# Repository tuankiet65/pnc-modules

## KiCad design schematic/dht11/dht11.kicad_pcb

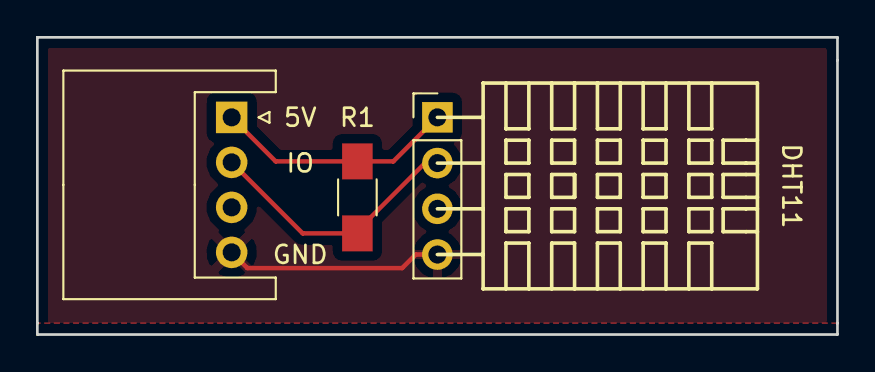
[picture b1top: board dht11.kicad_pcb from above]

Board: 2 copper layers, 44.5 x 16.5 mm, 3 parts (0 on the bottom side), 3 nets.

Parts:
J1: Conn_01x04; JST_XH_S04B-XH-A_04x2.50mm_Angled
R1: 10k; R_1206_HandSoldering
U1: DHT11; Pin_Header_Straight_1x04_Pitch2.54mm

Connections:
+5V: J1.1, R1.2, U1.1
/IO: J1.2, R1.1, U1.2
GND: J1.4, U1.4

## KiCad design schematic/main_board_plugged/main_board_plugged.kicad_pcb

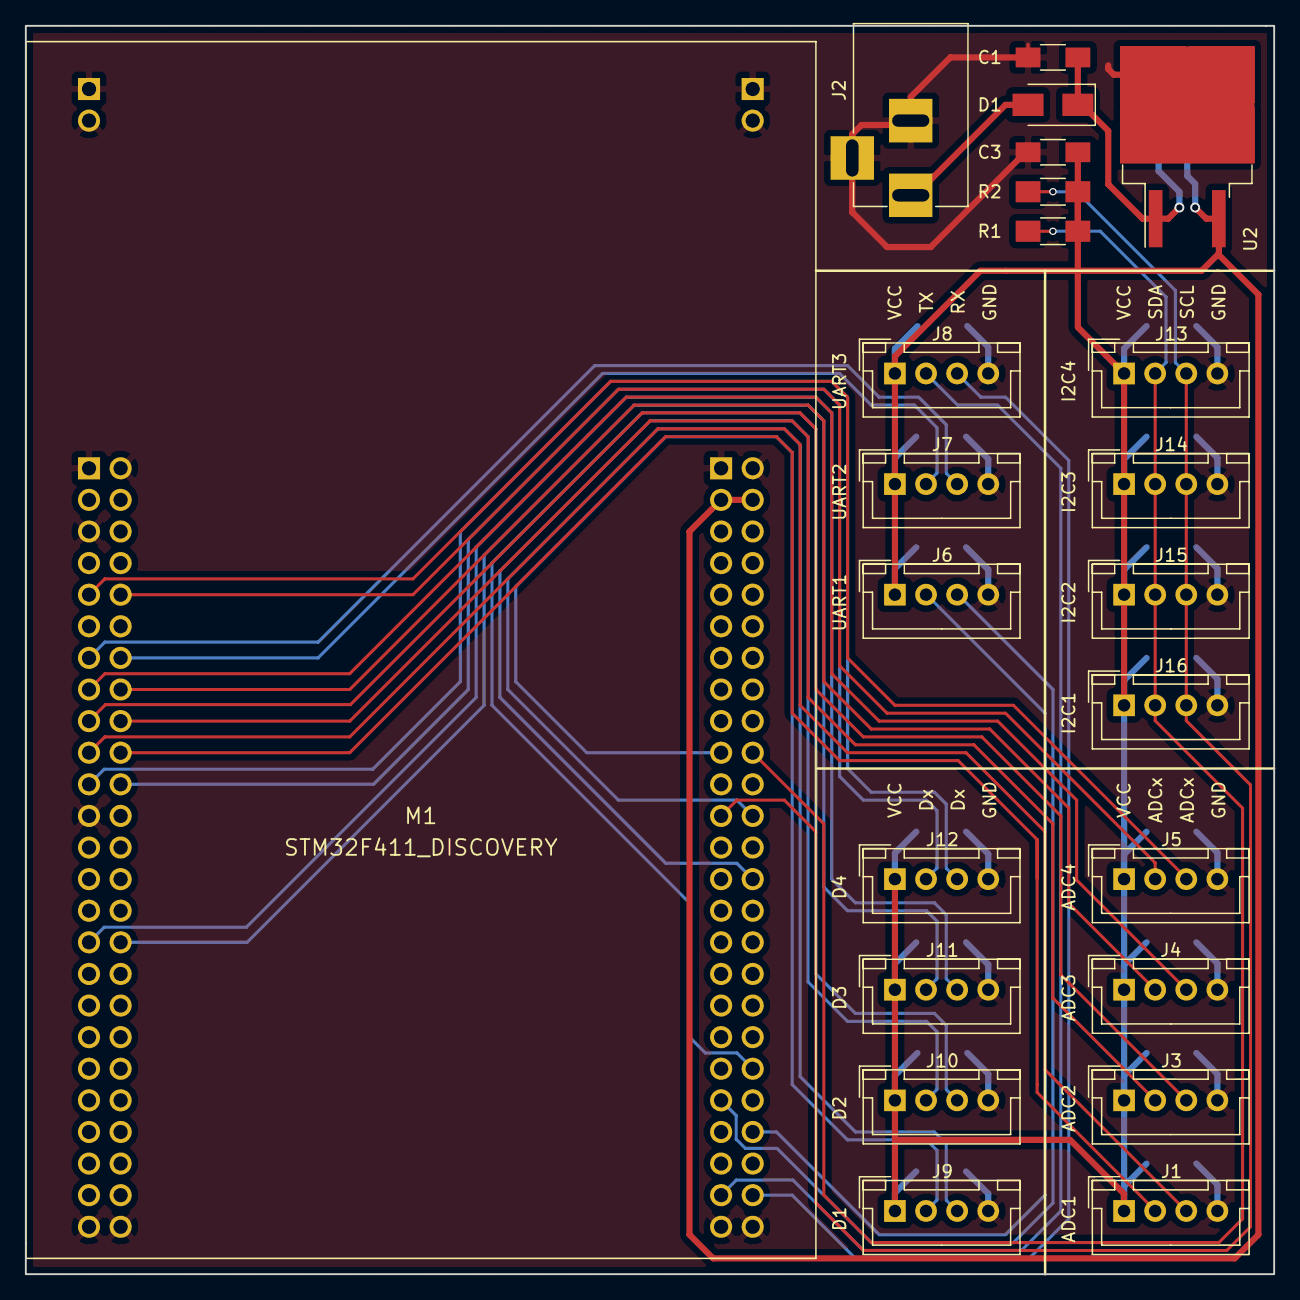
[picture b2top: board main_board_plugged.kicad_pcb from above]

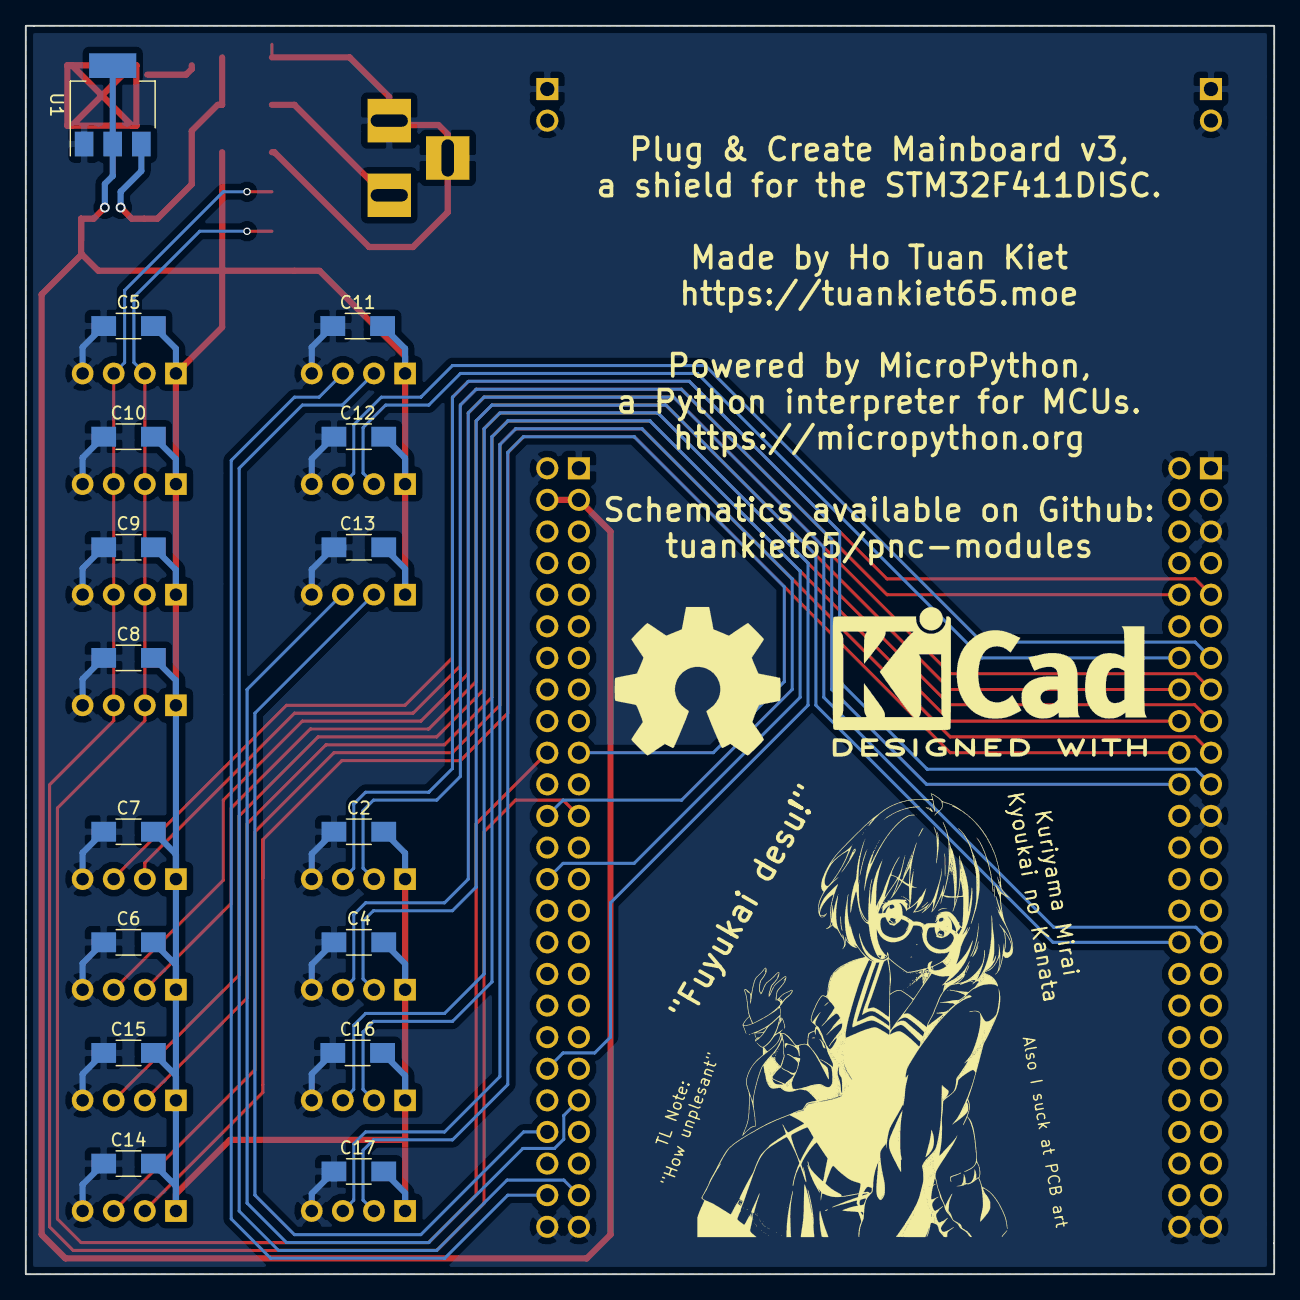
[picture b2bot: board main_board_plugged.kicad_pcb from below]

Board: 2 copper layers, 100.3 x 100.3 mm, 39 parts (16 on the bottom side), 28 nets.

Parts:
C1, C2, C4, C5, C6, C7, C8, C9, C10, C11, C12, C13, C14, C15, C16, C17: 100n; C_1206_HandSoldering
C3: 10u; C_1206_HandSoldering
D1: SS34; D_SMA
J1, J3, J4, J5, J6, J7, J8, J9, J10, J11, J12, J13, J14, J15, J16: Conn_01x04; JST_XH_B04B-XH-A_04x2.50mm_Straight
J2: Barrel_Jack; BARREL_JACK
M1: STM32F411_DISCOVERY; STM32F411_DISCOVERY-STM32F411_DISCOVERY
R1, R2: 10k; R_1206_HandSoldering
U1: LD1117S50TR_SOT223; SOT-223-3_TabPin2
U2: L7805; TO-263-2

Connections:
+5V: C2.1, C3.1, C4.1, C5.1, C6.1, C7.1, C8.1, C9.1, C10.1, C11.1, C12.1, C13.1, C14.1, C15.1, C16.1, C17.1, J1.1, J3.1, J4.1, J5.1, J6.1, J7.1, J8.1, J9.1, J10.1, J11.1, J12.1, J13.1, J14.1, J15.1, J16.1, M1.52, M1.77, R1.2, R2.2, U1.2, U2.3
/ADC1: J1.2, M1.35
/ADC2: J1.3, M1.10
/ADC3: J3.2, M1.34
/ADC4: J3.3, M1.9
/ADC5: J4.2, M1.33
/ADC6: J4.3, M1.8
/ADC7: J5.2, M1.30
/ADC8: J5.3, M1.5
/D1: J9.2, M1.60
/D2: J9.3, M1.87
/D3: J10.2, M1.89
/D4: J10.3, M1.95
/D5: J11.2, M1.41
/D6: J11.3, M1.16
/D7: J12.2, M1.36
/D8: J12.3, M1.11
/I2C1_SCL: J13.3, J14.3, J15.3, J16.3, M1.62, R2.1
/I2C1_SDA: J13.2, J14.2, J15.2, J16.2, M1.85, R1.1
/RX1: J6.3, M1.71
/RX2: J7.3, M1.7
/RX3: J8.3, M1.99
/TX1: J6.2, M1.97
/TX2: J7.2, M1.32
/TX3: J8.2, M1.74
GND: C1.2, C2.2, C3.2, C4.2, C5.2, C6.2, C7.2, C8.2, C9.2, C10.2, C11.2, C12.2, C13.2, C14.2, C15.2, C16.2, C17.2, J1.4, J2.2, J2.3, J3.4, J4.4, J5.4, J6.4, J7.4, J8.4, J9.4, J10.4, J11.4, J12.4, J13.4, J14.4, J15.4, J16.4, M1.1, M1.3, M1.12, M1.25, M1.26, M1.50, M1.51, M1.75, M1.76, M1.100, M1.101, M1.102, M1.103, M1.104, U1.1, U2.2
unnamed: C1.1, D1.1, U1.3, U2.1
VCC: D1.2, J2.1

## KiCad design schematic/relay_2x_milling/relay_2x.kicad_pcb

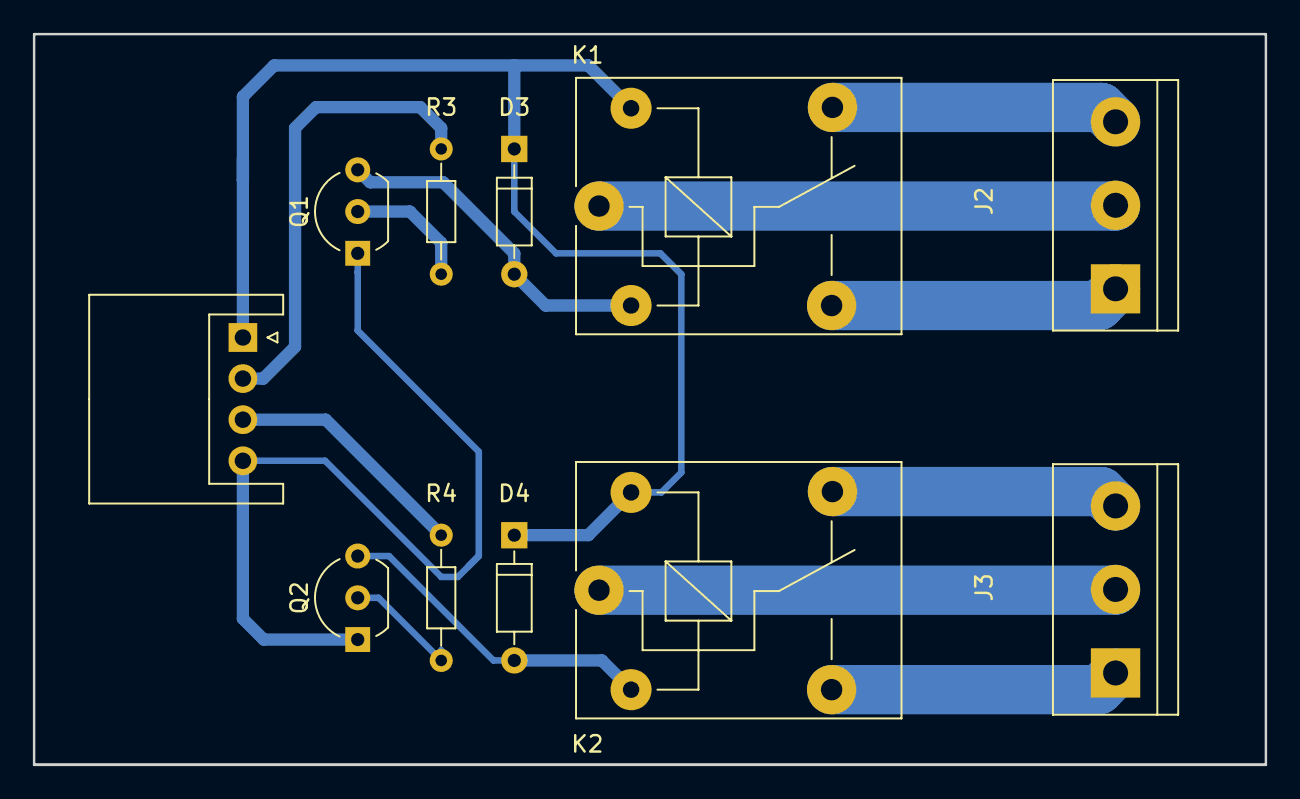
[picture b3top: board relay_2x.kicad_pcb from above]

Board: 2 copper layers, 74.9 x 44.5 mm, 11 parts (0 on the bottom side), 14 nets.

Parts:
D3, D4: 1N4007; D_DO-35_SOD27_P7.62mm_Horizontal
J1: Conn_01x04; JST_XH_S04B-XH-A_04x2.50mm_Angled
J2, J3: Conn_01x03; TerminalBlock_bornier-3_P5.08mm
K1, K2: SANYOU_SRD_Form_C; Relay_SPDT_SANYOU_SRD_Series_Form_C
Q1, Q2: 2N3904; TO-92_Inline_Wide
R3, R4: 1k; R_Axial_DIN0204_L3.6mm_D1.6mm_P7.62mm_Horizontal

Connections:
+5V: D3.1, D4.1, J1.1, K1.5, K2.5
/RELAY1: J1.2, R3.2
/RELAY2: J1.3, R4.2
GND: J1.4, Q1.1, Q2.1
unnamed: D3.2, K1.2, Q1.3
unnamed: D4.2, K2.2, Q2.3
unnamed: J2.1, K1.3
unnamed: J2.2, K1.1
unnamed: J2.3, K1.4
unnamed: J3.1, K2.3
unnamed: J3.2, K2.1
unnamed: J3.3, K2.4
unnamed: Q1.2, R3.1
unnamed: Q2.2, R4.1

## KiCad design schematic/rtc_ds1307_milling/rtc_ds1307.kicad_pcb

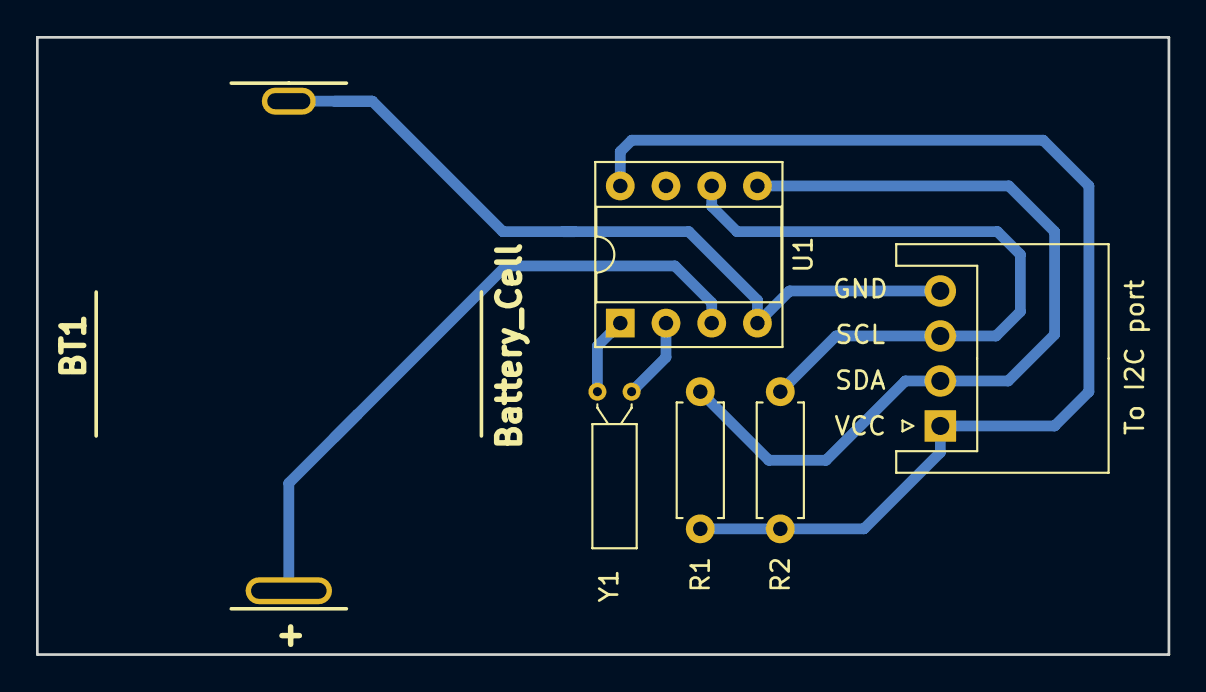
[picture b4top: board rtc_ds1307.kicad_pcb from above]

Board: 2 copper layers, 62.9 x 34.3 mm, 6 parts (0 on the bottom side), 7 nets.

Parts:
BT1: Battery_Cell; BC2032-E2
J1: Conn_01x04; JST_XH_S04B-XH-A_04x2.50mm_Angled
R1, R2: 10k; R_Axial_DIN0207_L6.3mm_D2.5mm_P7.62mm_Horizontal
U1: DS1307+; DIP-8_W7.62mm_Socket
Y1: 32768; Crystal_C26-LF_d2.1mm_l6.5mm_Horizontal

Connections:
+5V: J1.1, R1.1, R2.1, U1.8
+BATT: BT1.1, U1.3
-BATT: BT1.2, J1.4, U1.4
/SCL: J1.3, R2.2, U1.6
/SDA: J1.2, R1.2, U1.5
/XTAL1: U1.1, Y1.1
/XTAL2: U1.2, Y1.2

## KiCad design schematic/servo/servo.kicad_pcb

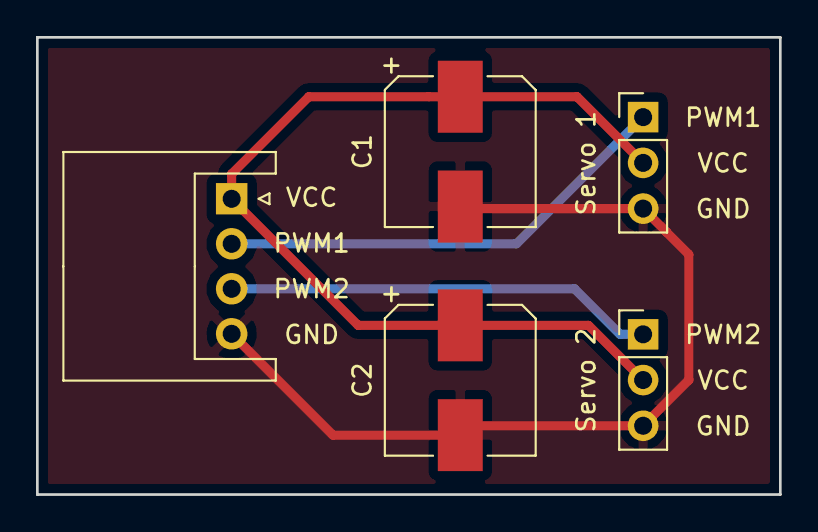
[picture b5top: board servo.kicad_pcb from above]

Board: 2 copper layers, 41.3 x 25.4 mm, 5 parts (0 on the bottom side), 4 nets.

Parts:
C1, C2: 470u; CP_Elec_8x10.5
J1: Conn_01x04; JST_XH_S04B-XH-A_04x2.50mm_Angled
M1: Servo1; Pin_Header_Straight_1x03_Pitch2.54mm
M2: Servo2; Pin_Header_Straight_1x03_Pitch2.54mm

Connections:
+5V: C1.1, C2.1, J1.1, M1.2, M2.2
/PWM1: J1.2, M1.1
/PWM2: J1.3, M2.1
GND: C1.2, C2.2, J1.4, M1.3, M2.3

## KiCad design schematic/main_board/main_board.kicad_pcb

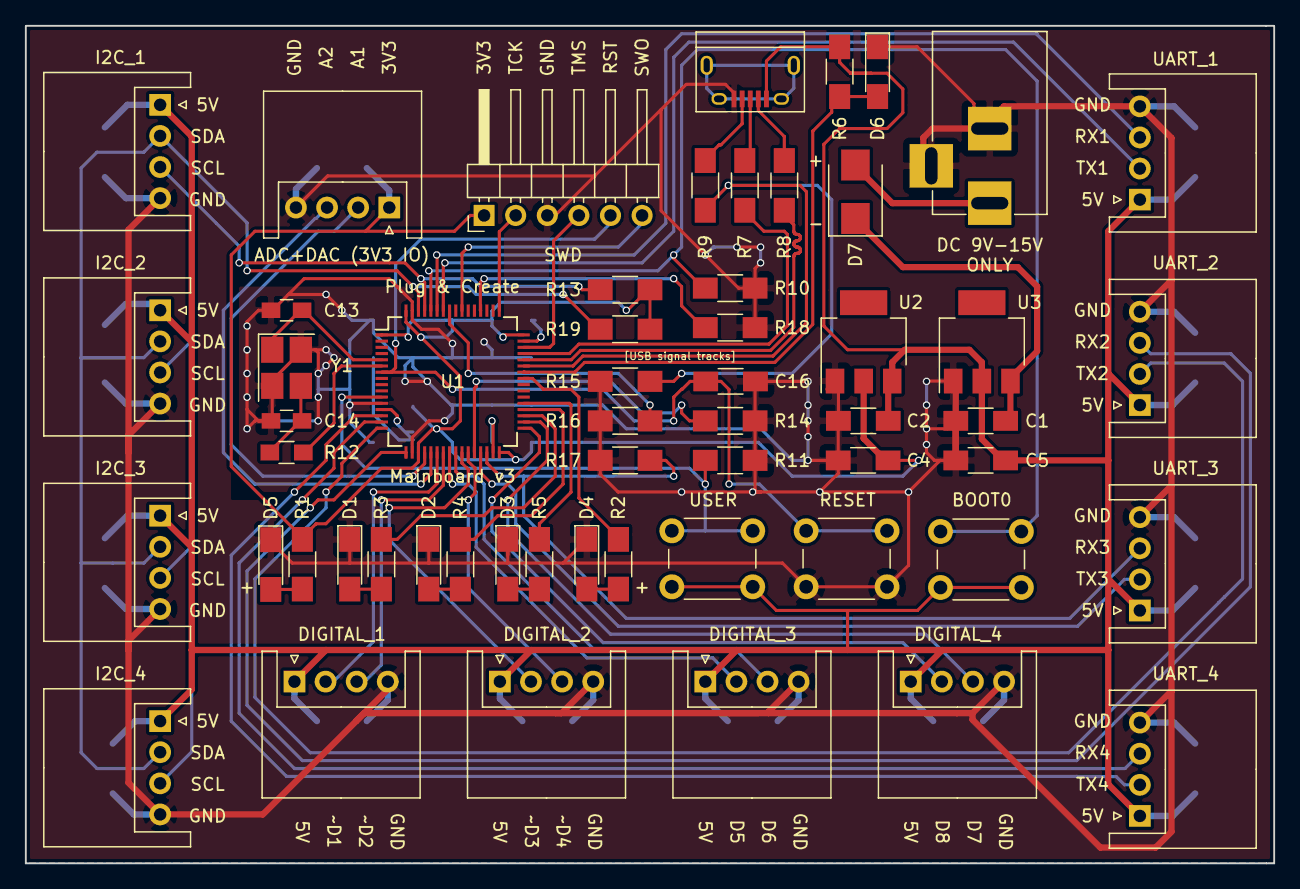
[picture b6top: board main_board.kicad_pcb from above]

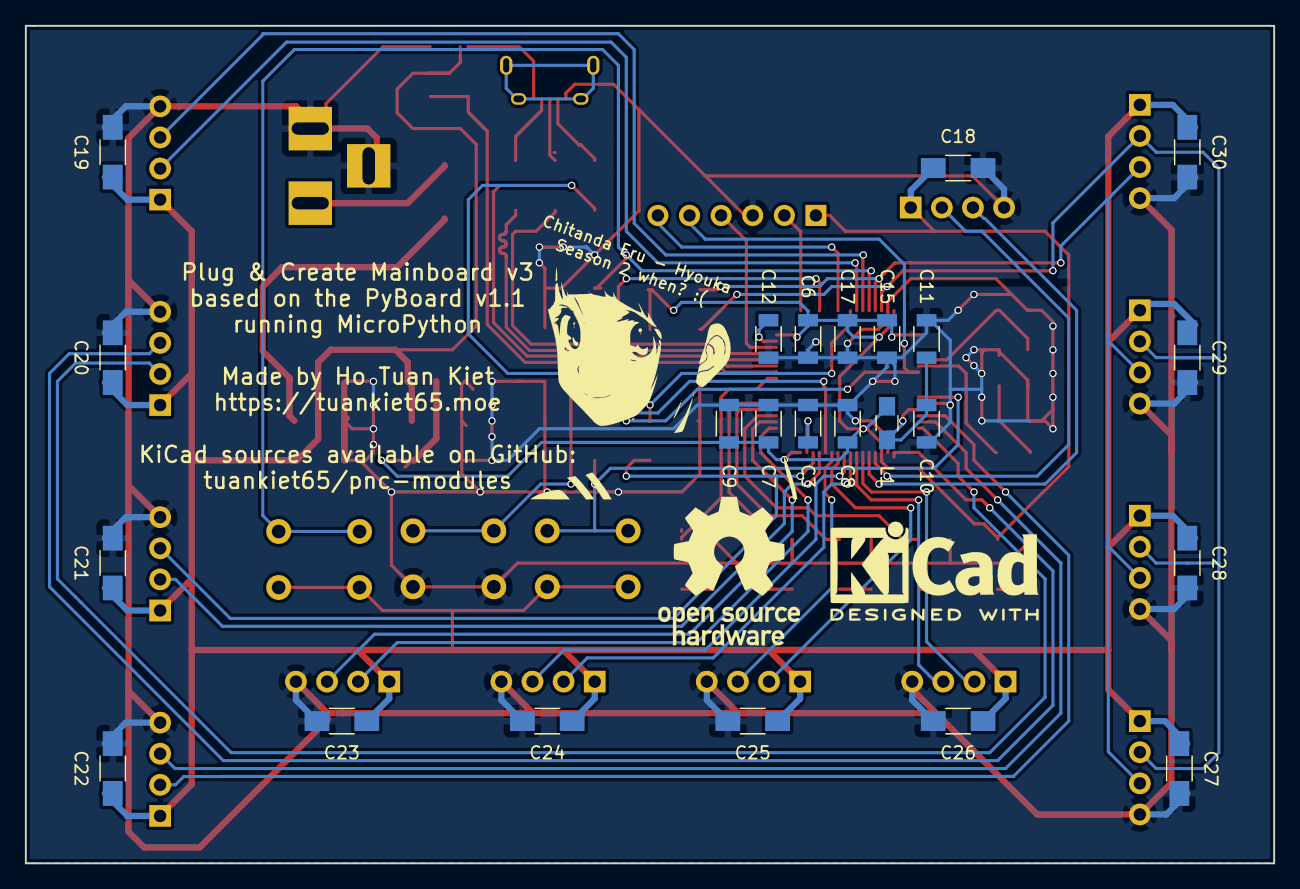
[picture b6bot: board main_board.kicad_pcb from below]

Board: 2 copper layers, 100.3 x 67.3 mm, 80 parts (24 on the bottom side), 56 nets.

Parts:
C1, C2, C16, C18, C19, C20, C21, C22, C23, C24, C25, C26, C27, C28, C29, C30: 100n; C_1206_HandSoldering
C3, C12: 2.2u; C_1206
C4, C5: 10u; C_1206_HandSoldering
C6, C7, C8, C10, C15, C17: 100n; C_1206
C9: 10u; C_1206
C11: 1u; C_1206
C13, C14: 5.6p; C_0805_HandSoldering
D1: RED; LED_1206_HandSoldering
D2, D5, D6: GREEN; LED_1206_HandSoldering
D3: BLUE; LED_1206_HandSoldering
D4: WHITE; LED_1206_HandSoldering
D7: SS34; D_SMB
J1: UART_1; JST_XH_S04B-XH-A_04x2.50mm_Angled
J2: UART_2; JST_XH_S04B-XH-A_04x2.50mm_Angled
J3: UART_3; JST_XH_S04B-XH-A_04x2.50mm_Angled
J4: UART_4; JST_XH_S04B-XH-A_04x2.50mm_Angled
J5: DIGITAL_1; JST_XH_S04B-XH-A_04x2.50mm_Angled
J6: DIGITAL_2; JST_XH_S04B-XH-A_04x2.50mm_Angled
J7: DIGITAL_3; JST_XH_S04B-XH-A_04x2.50mm_Angled
J8: DIGITAL_4; JST_XH_S04B-XH-A_04x2.50mm_Angled
J9: I2C_1; JST_XH_S04B-XH-A_04x2.50mm_Angled
J10: I2C_2; JST_XH_S04B-XH-A_04x2.50mm_Angled
J11: I2C_3; JST_XH_S04B-XH-A_04x2.50mm_Angled
J12: I2C_4; JST_XH_S04B-XH-A_04x2.50mm_Angled
J13: USB_OTG; USB_Micro-B
J14: ANALOG; JST_XH_S04B-XH-A_04x2.50mm_Angled
J15: SWD; Pin_Header_Angled_1x06_Pitch2.54mm
J17: Barrel_Jack; BARREL_JACK
L1: 600; L_0805_HandSoldering
R1, R2, R3, R4, R5: 220; R_1206_HandSoldering
R6, R9: 560; R_1206_HandSoldering
R7, R8: 22; R_1206_HandSoldering
R10, R11, R13, R14, R15, R16, R17, R18, R19: 10k; R_1206_HandSoldering
R12: 2k2; R_0805_HandSoldering
SW1: BOOT0; SW_PUSH_6mm
SW2: USR; SW_PUSH_6mm
SW3: RST; SW_PUSH_6mm
U1: STM32F405RGTx; LQFP-64_10x10mm_Pitch0.5mm
U2: LD1117S33CTR; SOT-223
U3: LD1117S50CTR; SOT-223
Y1: 12MHz; Crystal_SMD_3225-4pin_3.2x2.5mm_HandSoldering

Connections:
+3V3: C4.1, C6.1, C7.1, C8.1, C9.1, C15.1, C17.1, C18.1, J14.1, J15.1, L1.1, R1.2, R13.1, R19.1, U1.1, U1.19, U1.32, U1.48, U1.64, U2.2
+5V: C2.1, C5.1, C19.1, C20.1, C21.1, C22.1, C23.1, C24.1, C25.1, C26.1, C27.1, C28.1, C29.1, C30.1, J1.1, J2.1, J3.1, J4.1, J5.1, J6.1, J7.1, J8.1, J9.1, J10.1, J11.1, J12.1, J13.1, R6.2, SW1.2, SW2.2, U2.3, U3.2
/ANALOG1: J14.2, U1.20
/ANALOG2: J14.3, U1.21
/BOOT0: R10.1, SW1.1, U1.60
/D1: J5.2, U1.22
/D2: J5.3, U1.23
/D3: J6.2, U1.26
/D4: J6.3, U1.27
/D5: J7.2, U1.24
/D6: J7.3, U1.25
/D7: J8.2, U1.33
/D8: J8.3, U1.34
/HSE_IN: C13.1, U1.5, Y1.1
/HSE_OUT: R12.1, U1.6
/I2C1_SCL: J9.3, J10.3, J11.3, J12.3, R13.2, U1.61
/I2C1_SDA: J9.2, J10.2, J11.2, J12.2, R19.2, U1.62
/JTCK_SWCLK: J15.2, U1.49
/JTDO_SWO: J15.6, U1.55
/JTMS_SWDIO: J15.4, U1.46
/LED_BLUE: R5.2, U1.37
/LED_GREEN: R4.2, U1.36
/LED_RED: R3.2, U1.35
/LED_WHITE: R2.2, U1.41
/MICROSD_D3: R18.2, U1.52
/NRST: C16.1, J15.5, SW3.1, U1.7
/PB5: R16.2, U1.57
/RX1: J1.3, U1.59
/RX2: J2.3, U1.17
/RX3: J3.3, R17.2, U1.30
/RX4: J4.3, U1.15
/TX1: J1.2, U1.58
/TX2: J2.2, U1.16
/TX3: J3.2, U1.29
/TX4: J4.2, U1.14
/USB_D+: R7.1, U1.45
/USB_D-: R8.1, U1.44
/USB_ID: R9.1, R15.2, U1.43
/USB_VBUS: D6.2, R6.1, U1.42
/USER_BUTTON: R11.1, SW2.1, U1.11
/VCAP1: C3.1, U1.31
/VCAP2: C12.1, U1.47
GND: C1.2, C2.2, C3.2, C4.2, C5.2, C6.2, C7.2, C8.2, C9.2, C10.2, C11.2, C12.2, C13.2, C14.2, C15.2, C16.2, C17.2, C18.2, C19.2, C20.2, C21.2, C22.2, C23.2, C24.2, C25.2, C26.2, C27.2, C28.2, C29.2, C30.2, D1.1, D2.1, D3.1, D4.1, D5.1, D6.1, J1.4, J2.4, J3.4, J4.4, J5.4, J6.4, J7.4, J8.4, J9.4, J10.4, J11.4, J12.4, J13.5, J14.4, J15.3, J17.2, J17.3, R10.2, R11.2, R14.1, R15.1, R16.1, R17.1, R18.1, SW3.2, U1.12, U1.18, U1.63, U2.1, U3.1, Y1.2, Y1.4
unnamed: C1.1, D7.1, U3.3
unnamed: C14.1, R12.2, Y1.3
unnamed: D1.2, R3.1
unnamed: D2.2, R4.1
unnamed: D3.2, R5.1
unnamed: D4.2, R2.1
unnamed: D5.2, R1.1
unnamed: D7.2, J17.1
unnamed: J13.2, R8.2
unnamed: J13.3, R7.2
unnamed: J13.4, R9.2
unnamed: R14.2, U1.28
VDDA: C10.1, C11.1, L1.2, U1.13

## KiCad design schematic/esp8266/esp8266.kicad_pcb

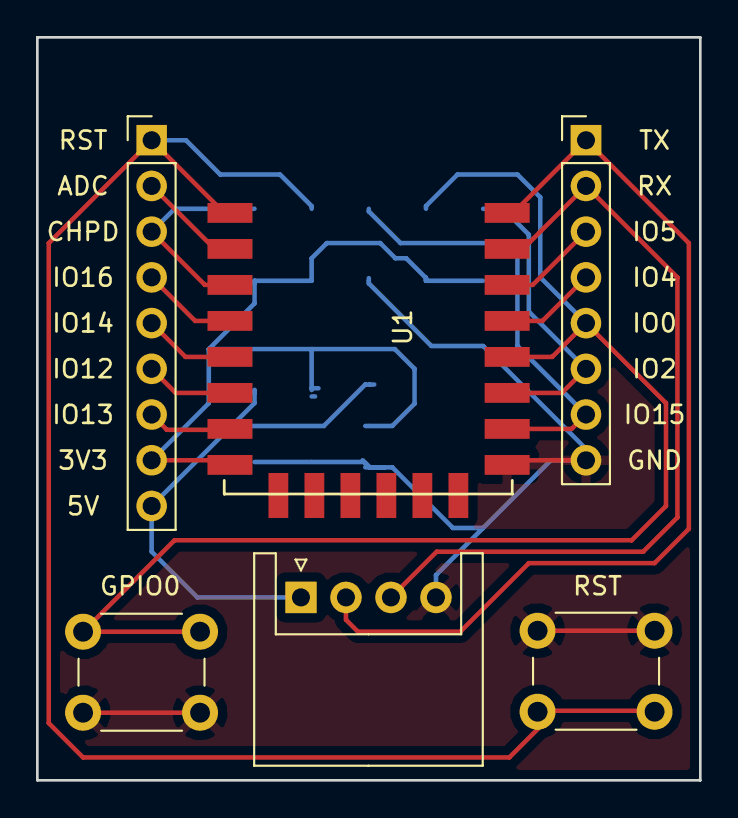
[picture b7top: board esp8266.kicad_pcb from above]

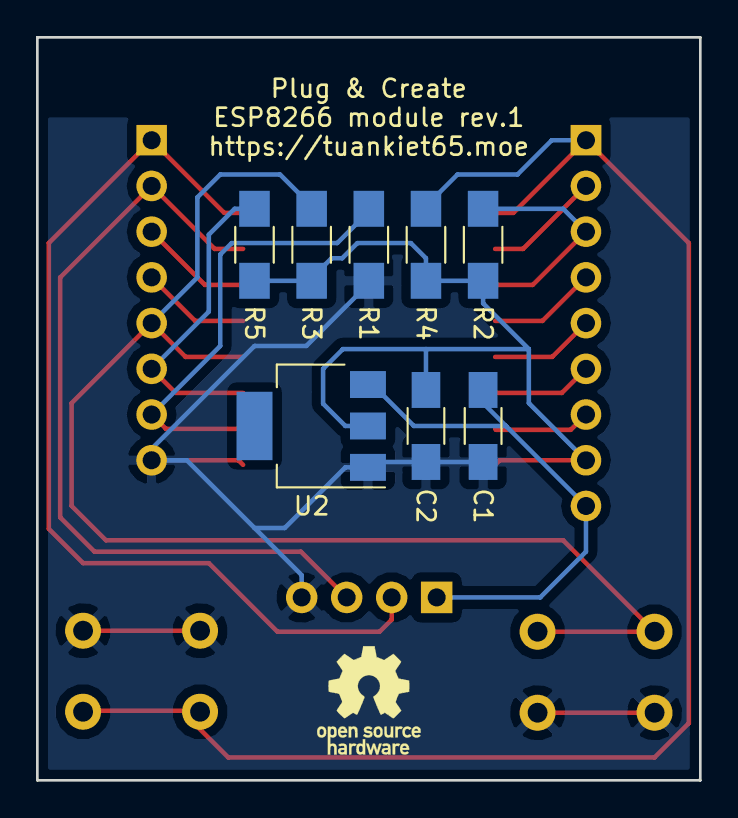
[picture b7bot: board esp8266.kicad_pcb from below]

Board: 2 copper layers, 36.8 x 41.3 mm, 14 parts (8 on the bottom side), 17 nets.

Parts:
C1: 100n; C_1206_HandSoldering
C2: 10u; C_1206_HandSoldering
J1: CONNECTOR; JST_XH_S04B-XH-A_04x2.50mm_Angled
J3: ROW_1; Pin_Header_Straight_1x09_Pitch2.54mm
J4: ROW_2; Pin_Header_Straight_1x08_Pitch2.54mm
R1, R2, R3, R4, R5: 10k; R_1206_HandSoldering
SW1: RST; SW_PUSH_6mm
SW2: FLASH_PROG; SW_PUSH_6mm
U1: ESP-12E; ESP-12E_SMD
U2: LD1117S33CTR; SOT-223

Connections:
+3V3: C2.1, J3.8, R2.1, R3.1, R4.1, R5.1, U1.8, U2.2
+5V: C1.1, J1.1, J3.9, U2.3
/ADC: J3.2, U1.2
/CH_PD: J3.3, R2.2, U1.3
/GPIO0: J4.5, R3.2, SW2.1, U1.12
/GPIO2: J4.6, R5.2, U1.11
/GPIO4: J4.4, U1.13
/GPIO5: J4.3, U1.14
/GPIO12: J3.6, U1.6
/GPIO13: J3.7, U1.7
/GPIO14: J3.5, U1.5
/GPIO15: J4.7, R1.1, U1.10
/GPIO16: J3.4, U1.4
/RST: J3.1, R4.2, SW1.1, U1.1
/RX: J1.3, J4.2, U1.15
/TX: J1.2, J4.1, U1.16
GND: C1.2, C2.2, J1.4, J4.8, R1.2, SW1.2, SW2.2, U1.9, U2.1

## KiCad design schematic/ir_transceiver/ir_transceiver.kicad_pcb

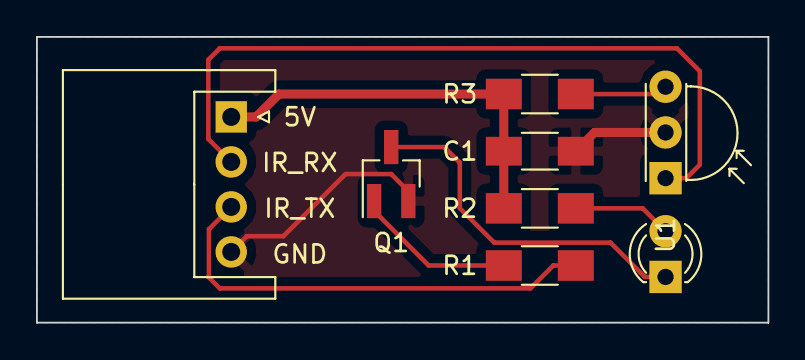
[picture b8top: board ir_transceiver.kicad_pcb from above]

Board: 2 copper layers, 40.6 x 15.9 mm, 8 parts (0 on the bottom side), 8 nets.

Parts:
C1: 10u; C_1206_HandSoldering
D1: IR204A; LED_D3.0mm
J1: Conn_01x04; JST_XH_S04B-XH-A_04x2.50mm_Angled
Q1: BC817; SOT-23_Handsoldering
R1: 2.2k; R_1206_HandSoldering
R2: 220; R_1206_HandSoldering
R3: 100; R_1206_HandSoldering
U1: TSOP331xx; IRReceiver_Vishay_MINIMOLD-3pin

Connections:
+5V: C1.1, J1.1, R2.1, R3.1
/IR_RX: J1.2, U1.1
/IR_TX: J1.3, R1.2
GND: C1.2, J1.4, Q1.2, U1.2
unnamed: D1.1, Q1.3
unnamed: D1.2, R2.2
unnamed: Q1.1, R1.1
unnamed: R3.2, U1.3

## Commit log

2017-06-24 _Serial now reads and writes bytes instead of data_packet
    The work of assembling data_packet is now in the main loop instead of in _Serial
2017-06-25 makefile: do not strip output elf
    There's no need to strip output binary as all symbols are ignored by avr-objcopy
2017-06-25 hd44780: new void _pin_write for writing to pins
    Avoid 'don't repeat yourself', also help to reduce code size
2017-06-25 protocol: reduce maximum data size to 8 byte
    8 byte ought be enough for most, and this helps reduce RAM usage
2017-06-25 uart/hard_uart: reduce buffer size to 10 byte
    In 1129d68, sizeof(data_packet) has been reduced to 10 bytes. We reduce the buffer size to accommodate for that change.
2017-06-25 makefile: change executable extension to .elf
    That feels right, also gitignore can ignore .elf extensions
2017-06-25 lcd_16x2_block: change if/then structure to switch/case
2017-06-25 lcd/hd44780: add support for backlight pin
2017-06-25 io: change if/then structure to switch/case
2017-06-28 uart/hard_uart: Enable UDR Ready Interrupt after incrementing tx_buf.tail
    Looks like if we do it before then characters will be lost/delayed.
    Examples:
    while(1){
    Serial.send('A');
    Serial.send('b');
    _delay_ms(1000);
2017-06-28 uart/hard_uart: Don't enable URDIE in initialization
    It will be enabled when the program executes a transmission
2017-06-28 New virtual class: Stream
    Stream is a virtual class for stream-like type (for example Serial)
    (idea copied from Arduino)
2017-06-28 New DataPacketStream class
    DataPackerStream is a Stream-like (although not really inherited from Stream) for packet data
2017-06-28 io: make some operations atomic
2017-06-28 lcd/hd44780: some code/data size optimizations
2017-06-28 lcd_16x2_block: Move to using DataPacketStream
2017-06-28 lcd_hd44780: Move LCD_START_ADDR to PROGMEM
2017-06-28 uart/hard_uart: increase buffer size to 8
    Hopefully we can make it to 10 (but that's unlikely)
2017-06-28 lcd/hd44780: enable brightness control using fake PWM
    "Fake PWM" because in the original schematic, the backlight pin is connected to PD6, which is not a Output Compare pin. As such we abuse the Timer's overflow/compare feature to fake a PWM.
    Due to this change, UART buffer size has to be decreased to 4 to accommodate for this change
2017-08-14 Add new numpad_4x4 module
2017-10-07 Mainboard
2017-10-07 Add PDF schematic
2017-10-07 Add top and bottom layer PDF
2017-10-07 Add top and bottom payer PDF with copper pour
2018-07-04 Committing everything
    Because my hard drive will soon crash and burn.o
